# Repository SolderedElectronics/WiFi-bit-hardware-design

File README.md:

# WiFi:bit Hardware Design

## About the Product

|  |
| :----------------------------------------------------------: |
| [Buy WiFi:bit](https://www.solde.red/333061) |

Micro:bit is a very interesting board with lots of options that are used by many children in school or hobbyists, but who can say no to new features! So we decided to make a micro:bit add-on that will enable internet connection via WiFi! Finally, you’ll be able to connect your micro:bit projects to the Internet and to connect to the well known Internet of Things. WiFi:bit add-on is easy to use through a MakeBlock add-on or using completed Python examples.

Just insert micro:bit to the add-on, plug in the power cable (required) and you are ready! Open the examples and start sending and receiving data from the internet. There are even two easyC connectors on the WiFi add-on, which allow the simplest connection of I2C sensors and actuators with micro:bit. There are also available pins on the board which are isolated on standard spacing used for breadboard connections or connections with cables to additional components!

---

## Repository Contents

This repository contains all design files for WiFi:bit, organized as follows:

- **`CAD` folder**: Contains KiCAD design files, including:
  - Schematics
  - PCB layout
  - Panel PCB layout
  - Source 3D files in Fusion360, if any
  - All files are sorted by version with a detailed change log.
- **`OUTPUTS` folder**: Includes all production-ready files, such as:
  - Bill of Materials (BOM) and interactive BOM (iBOM)
  - PDF versions of schematics
  - 3D `.step` file of the board
  - 3D-printable models
  - Gerber files for PCB manufacturing
  - Image of the pinout of the board
  - Product image
  - Compliance, legal and generic sales documents

Refer to the `Change Log` in the CAD folder for details about updates between versions.

---

## Learn More About the Product

Beyond the repository, explore the following resources:

### Soldered Verify

The **Soldered Verify** system ensures every board you purchase from Soldered is fully functional. It also provides access to exclusive test data for your product. To get started, find the unique Soldered Verify ID on your product's packaging and enter the ID on the [Soldered Verify page](https://soldered.com/verify/) to access test results and additional product details.

### Soldered Community

Soldered Community is your go-to place for technical support. Our engineers track and answer all questions posted there, and it’s a great space for the maker community. Get answers to your questions and solutions for your challenges at [Soldered Community](https://soldered.com/community).

### solde.red

solde.red is an ultimate URL shortener and information hub. Access it by typing solde.red/ followed by your product SKU, e.g., [solde.red/333000](https://solde.red/333000), to find getting-started guides, datasheets, open-source hardware and software files, certifications, images, pinouts, and more. Read more about the shortener [here](https://solde.red/info/).

---

## Contributing

Contributions are welcome! Here’s how you can get involved:

- Submit pull requests to enhance the design or fix issues.
- Report bugs or problems by opening an issue.

We encourage community collaboration to make this product even better.

---

## About Soldered

[Soldered for Makers](https://soldered.com) specializes in designing and manufacturing electronic products tailored for enthusiasts, ranging from hobbyists to professionals. Our portfolio includes electronic boards, sensors, and actuators that are widely utilized in fields such as microelectronics, mechatronics, robotics, programming, and IoT. Every product we offer is designed in-house and built upon open-source hardware and software platforms. Proudly certified and manufactured within the European Union, our catalog likely includes the product you need for your project.

We complement these products with comprehensive tutorials and manuals, product descriptions, schematics, programming codes, and project examples. Our round-the-clock [customer and technical support](https://soldered.com/community) is available for all our products, irrespective of the sales channel. Soldered’s success and services reflect our maker community’s unwavering [trust](https://www.trustpilot.com/review/soldered.com), for which we are deeply grateful. Join our community and create using Soldered products.

---

## License

All Soldered open-source hardware (OSH) is under The TAPR Open Hardware License. Read more in the LICENSE file located in this repository.

**Disclaimer:**

No warranty - all designs in this repository are distributed in the hope that they will be useful, but without any warranty. They are provided "AS IS", therefore without warranty of any kind, either expressed or implied. The entire quality and performance of what you do with the contents of this repository are your responsibility. In no event Soldered Electronics will be liable for your damages, or losses, including any general, special, incidental, or consequential damage arising out of the use or inability to use the contents of this repository. 

---

## Have fun!

Thank you for your support from your fellow makers at Soldered Electronics.

Happy Making!

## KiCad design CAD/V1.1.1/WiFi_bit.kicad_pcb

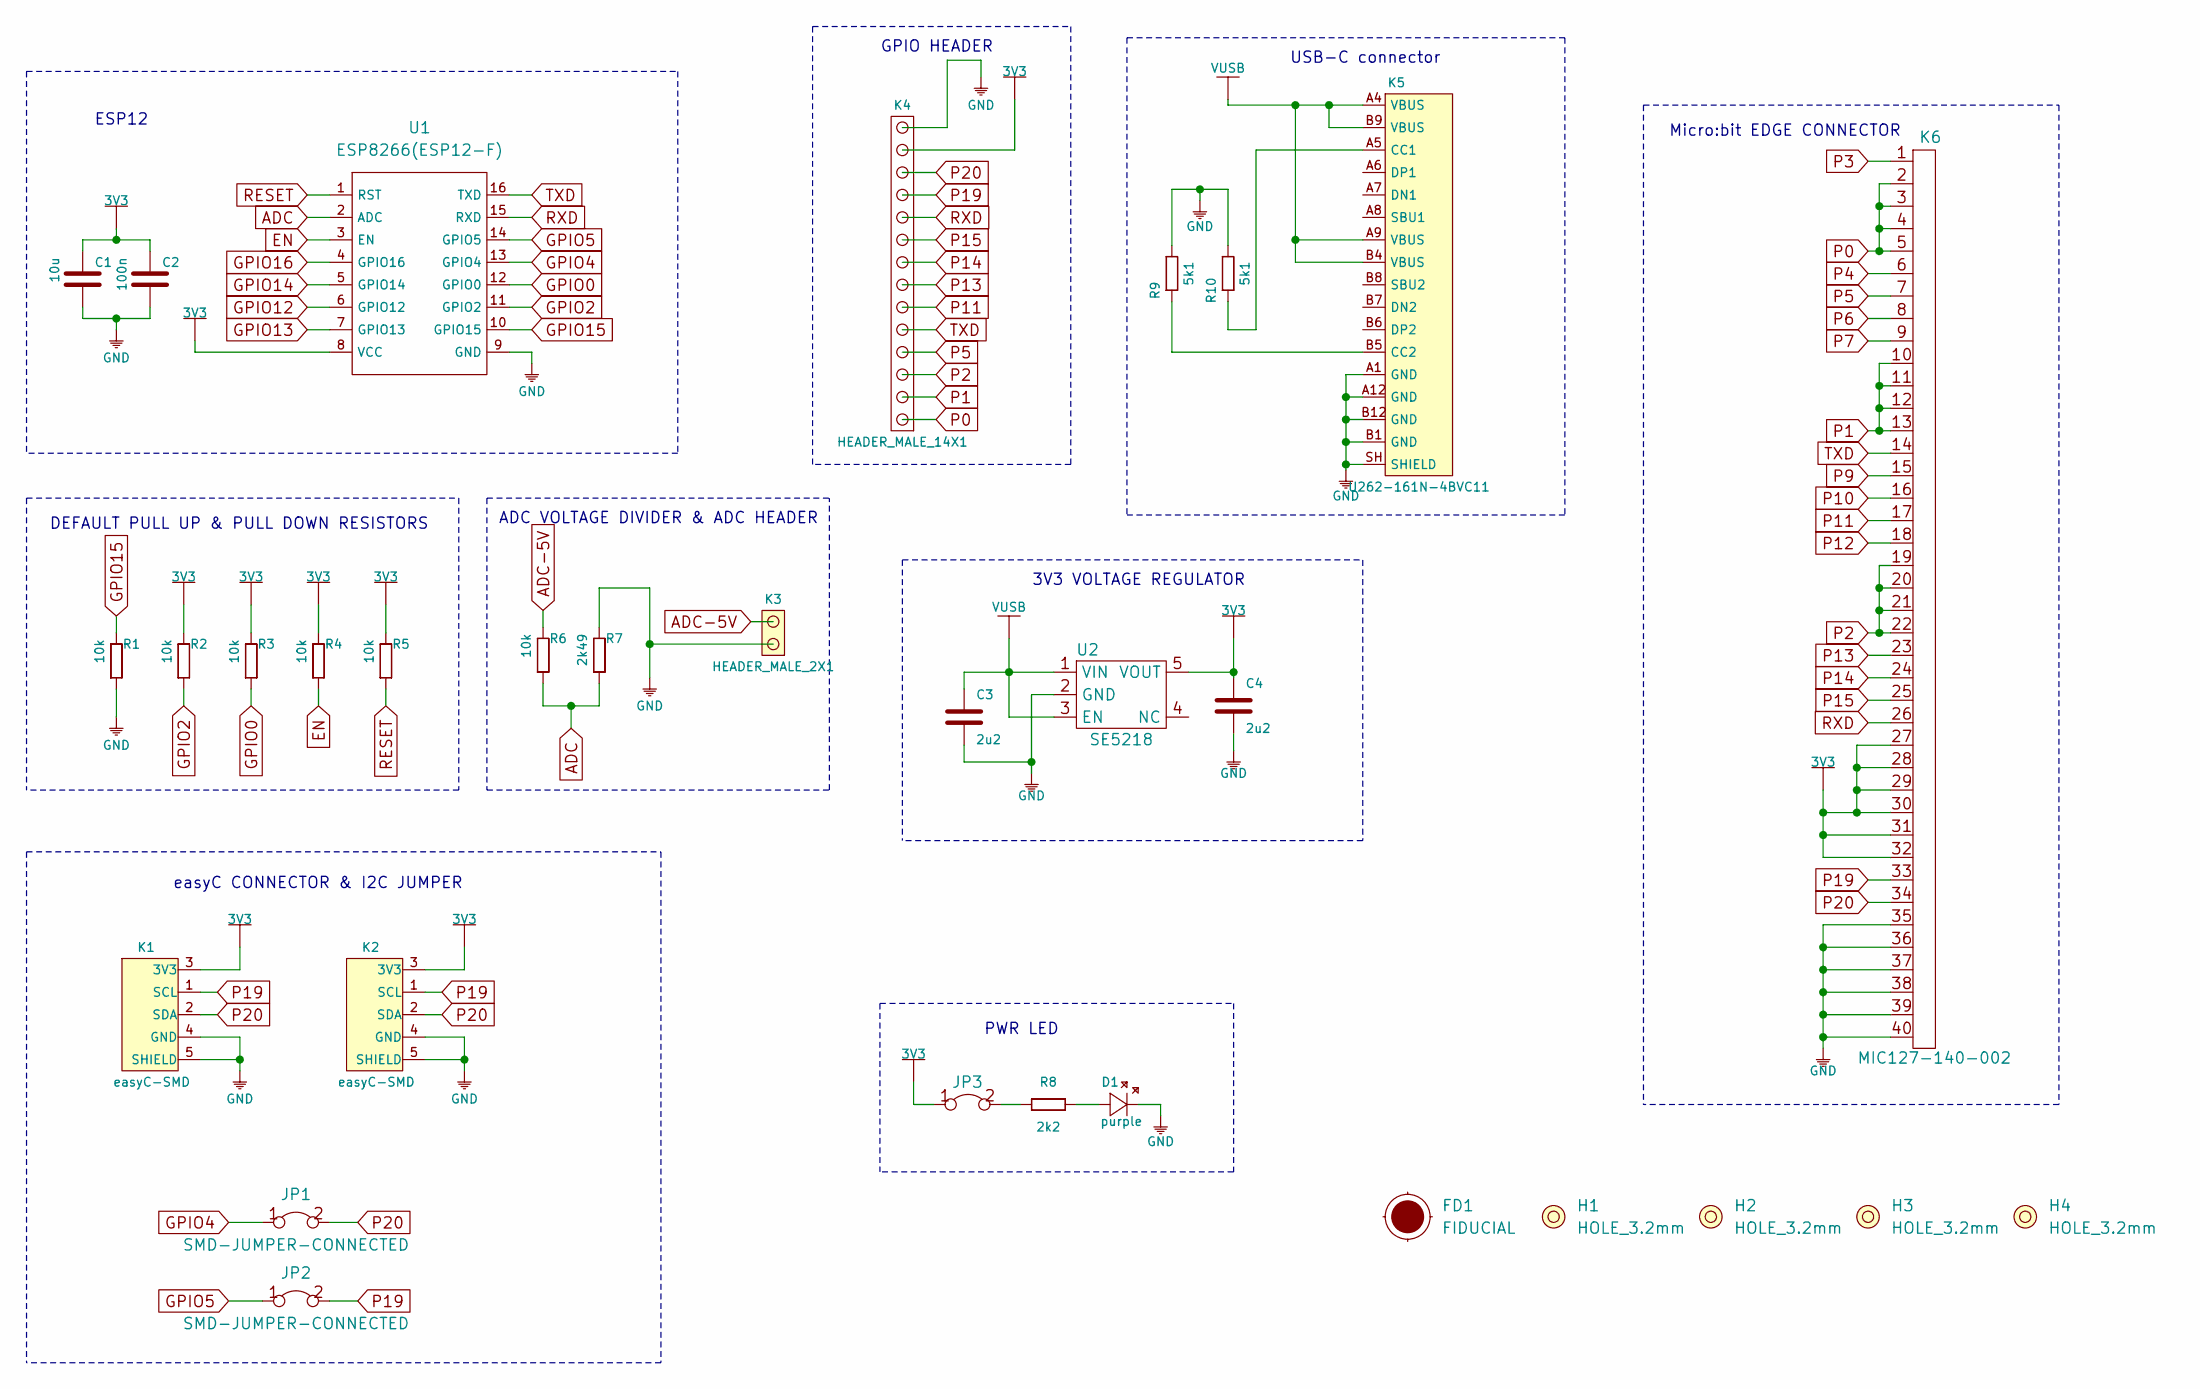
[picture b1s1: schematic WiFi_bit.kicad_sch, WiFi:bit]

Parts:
C1: 10u; 1206C
C2: 100n; 0603C
C3, C4: 2u2; 0603C
D1: purple; 0402LED
FD1: FIDUCIAL; FIDUCIAL_23
H1, H2, H3, H4: HOLE_3.2mm
JP1, JP2: SMD-JUMPER-CONNECTED; SMD_JUMPER_CONNECTED
JP3: SMD-JUMPER-CONNECTED_TRACE_SLODERMASK
K1, K2: easyC-SMD; easyC-connector
K3: HEADER_MALE_2X1
K4: HEADER_MALE_14X1
K5: U262-161N-4BVC11
K6: MIC127-140-002; MC127-140-002
R1, R2, R3, R4, R5, R6: 10k; 0603R
R7: 2k49; 0603R
R8: 2k2; 0402R
R9, R10: 5k1; 0603R
U1: ESP8266(ESP12-F); ESP 8266(ESP12-F)
U2: SE5218; SOT-23-5

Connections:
3V3: C1.2, C2.2, C4.2, JP3.1, K1.3 (3V3), K2.3 (3V3), K4.13, K6.27, K6.28, K6.29, K6.30, K6.31, K6.32, R2.2, R3.2, R4.2, R5.2, U1.8 (VCC), U2.5 (VOUT)
ADC: R6.1, R7.1, U1.2 (ADC)
ADC-5V: K3.2, R6.2
EN: R4.1, U1.3 (EN)
GND: C1.1, C2.1, C3.1, C4.1, D1.2 (K), K1.4 (GND), K1.5 (SHIELD), K2.4 (GND), K2.5 (SHIELD), K3.1, K4.14, K5.A1 (GND), K5.A12 (GND), K5.B1 (GND), K5.B12 (GND), K5.SH (SHIELD), K6.35, K6.36, K6.37, K6.38, K6.39, K6.40, R1.1, R7.2, R9.2, R10.2, U1.9 (GND), U2.2 (GND)
GPIO0: R3.1, U1.12 (GPIO0)
GPIO2: R2.1, U1.11 (GPIO2)
GPIO4: JP1.1, U1.13 (GPIO4)
GPIO5: JP2.1, U1.14 (GPIO5)
GPIO12: U1.6 (GPIO12)
GPIO13: U1.7 (GPIO13)
GPIO14: U1.5 (GPIO14)
GPIO15: R1.2, U1.10 (GPIO15)
GPIO16: U1.4 (GPIO16)
unnamed: D1.1 (A), R8.2
unnamed: JP3.2, R8.1
unnamed: K5.A5 (CC1), R10.1
unnamed: K5.B5 (CC2), R9.1
P0: K4.1, K6.2, K6.3, K6.4, K6.5
P1: K4.2, K6.10, K6.11, K6.12, K6.13
P2: K4.3, K6.19, K6.20, K6.21, K6.22
P3: K6.1
P4: K6.6
P5: K4.4, K6.7
P6: K6.8
P7: K6.9
P9: K6.15
P10: K6.16
P11: K4.6, K6.17
P12: K6.18
P13: K4.7, K6.23
P14: K4.8, K6.24
P15: K4.9, K6.25
P19: JP2.2, K1.1 (SCL), K2.1 (SCL), K4.11, K6.33
P20: JP1.2, K1.2 (SDA), K2.2 (SDA), K4.12, K6.34
RESET: R5.1, U1.1 (RST)
RXD: K4.10, K6.26, U1.15 (RXD)
TXD: K4.5, K6.14, U1.16 (TXD)
VUSB: C3.2, K5.A4 (VBUS), K5.A9 (VBUS), K5.B4 (VBUS), K5.B9 (VBUS), U2.1 (VIN), U2.3 (EN)

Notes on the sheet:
PWR LED
ESP12
Micro:bit EDGE CONNECTOR
3V3 VOLTAGE REGULATOR
easyC CONNECTOR & I2C JUMPER
ADC VOLTAGE DIVIDER & ADC HEADER
USB-C connector
DEFAULT PULL UP & PULL DOWN RESISTORS
GPIO HEADER

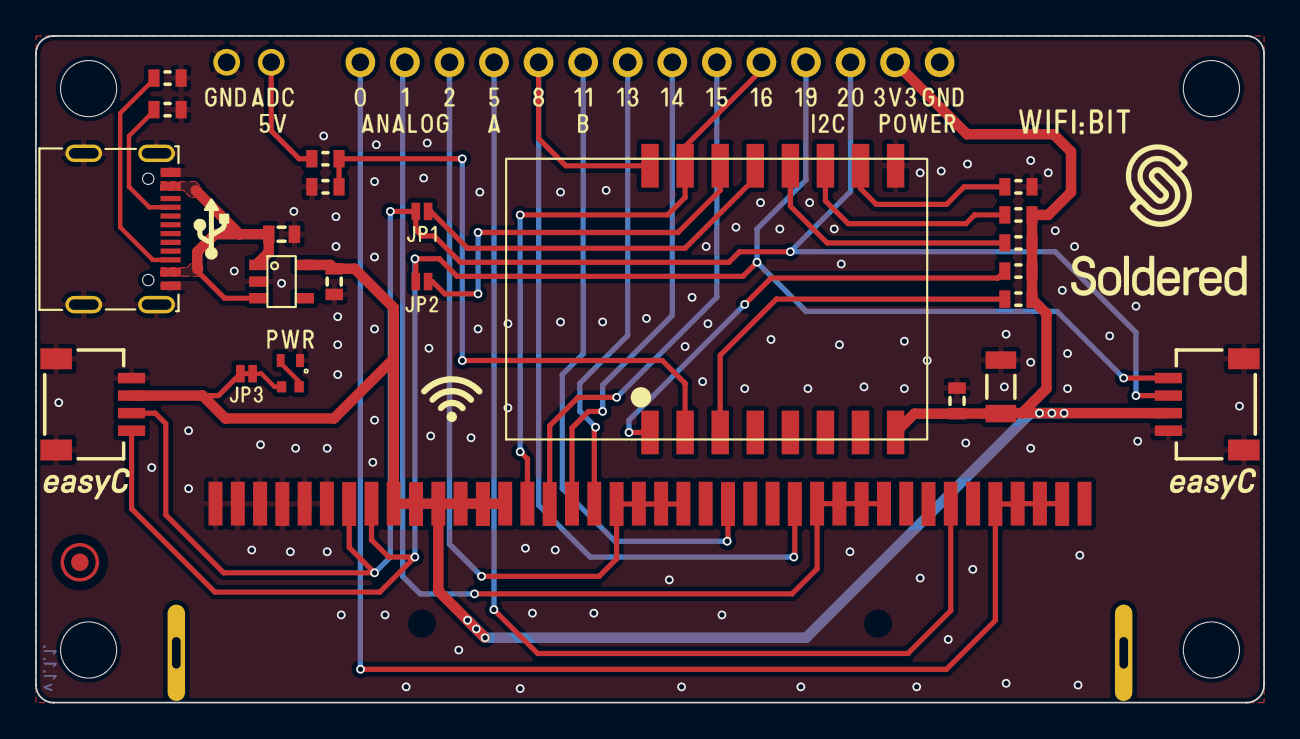
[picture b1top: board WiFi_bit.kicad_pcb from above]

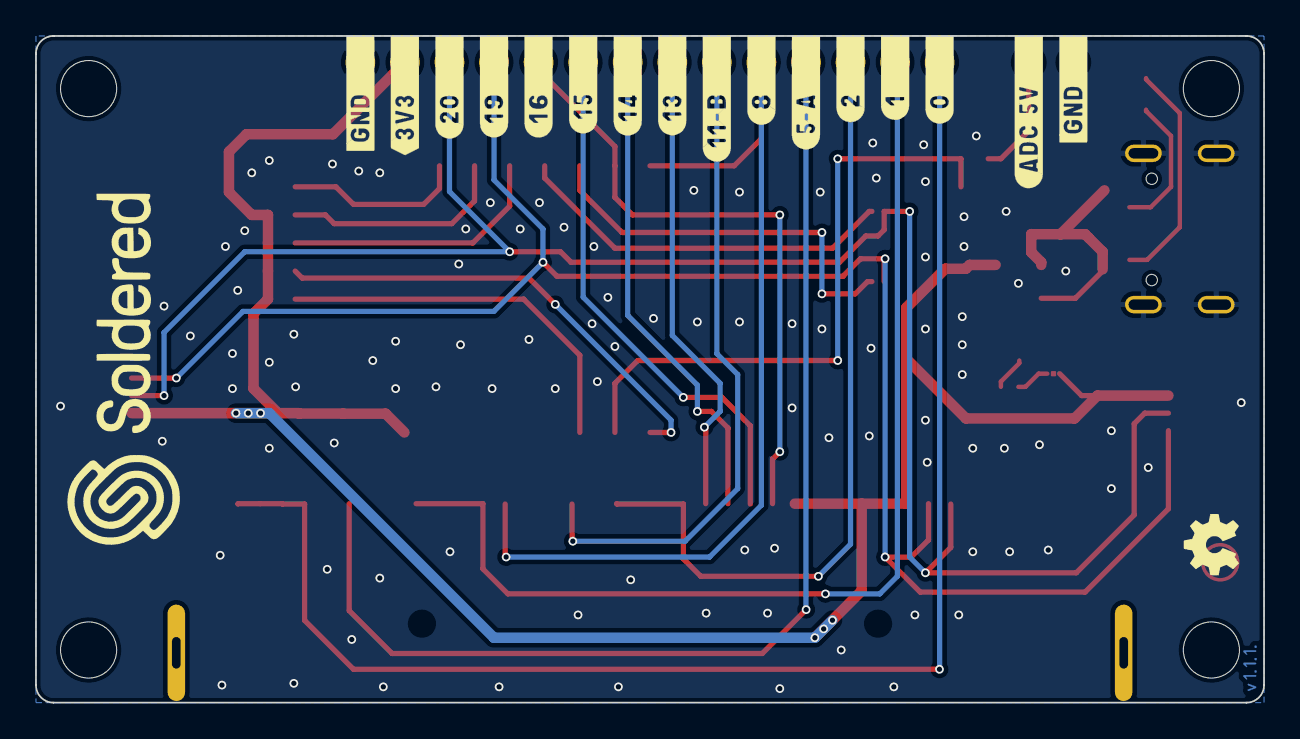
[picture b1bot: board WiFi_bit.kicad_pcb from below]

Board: 2 copper layers, 70.0 x 38.0 mm, 31 parts (2 on the bottom side), 28 nets.

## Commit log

2022-08-06 Updating open source files.
